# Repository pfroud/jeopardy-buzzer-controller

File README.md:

# Jeopardy buzzer controller

## About

For use with my [Jeopardy software](https://github.com/pfroud/jeopardy).

This device uses an Arduino to emulate a USB HID keyboard (like a QWERTY keyboard not a music keyboard). Instead of normal keyboard keys, the inputs come from rugged metal footswitches on long cables.

The sole purpose of this device is to convert physical button presses into USB HID keystrokes. It cannot tell which person buzzed first for a question, for example. All of that logic is done by software running on the host PC.

The PCB was designed using KiCad version 6 and fabricated by JLCPCB.

## Parts

The two most interesting parts are:

* [Sparkfun Pro Micro](https://www.sparkfun.com/products/12640) (not Mini, not Nano)
    * Informally called "Arduino Pro Micro" but it's actually a Sparkfun product which is Arduino-compatible.
    * To learn about the software running on the Arduino, see the [Arduino directory](Arduino).
* [XLR receptacle NC4MBV](https://www.neutrik.com/en/product/nc4mbv-1) to connect the buzzers.
    * To learn more, go to the "XLR connectors" section in this document.

Other parts:

* [12-pin female headers](https://www.aliexpress.us/item/2255801012106911.html) to hold the Arduino.
    * The Arduino could instead be soldered directly to the PCB if you're feeling confident.
* A toggle switch to enable/disable the Arduino software.
    * Lets you turn the buzzers off without unplugging the USB cable.
* [Panel-mount LED lights](https://www.aliexpress.com/item/3256803816108154.html) to indicate when it's powered and enabled.
* [2-pin pluggable terminal blocks](https://www.aliexpress.us/item/2251832631116561.html) to connect the toggle switch and indicator LEDs to the PCB.
* A 6mm tactile pushbutton to reset the Arduino.
    * The Pro Micro does not have a built-in reset button.

Then everything gets assembled into an [enclosure](docs/enclosure.md).

## Buzzers

On the Jeopardy TV show each contestant holds a thumb-operated buzzer ([source](https://www.jeopardy.com/jbuzz/behind-scenes/how-does-jeopardy-buzzer-work)).

My game has teams instead of individual players, so the buzzers rest on a table for access by all team members. I got rugged metal footswitches to withstand being slammed when someone thinks of an answer.

I started with Treadlite footswitches from at HSC Electronics (RIP) then got some TEMCo ones from [eBay](https://www.ebay.com/itm/372481343124).

On each footswitch I had to grind down the metal housing a little to fit a [PG7 cord grip](https://www.ebay.com/itm/222727122407). (PG stands for [Panzergewinde](https://en.wikipedia.org/wiki/Panzergewinde) which is an old German thread standard inexplicably still in use.)

The Treadlite model (below left) has a seemingly-custom switch mechanism inside, while the TEMCo model (below right) has a standard limit switch. The Treadlite ones originally come with *two* switches mounted at different heights but I removed the lower ones. The cable I used has a foil shield so I connected the drain wire to the metal housing for fun.

Eight buzzers are supported although I rarely use more than six.

## Known bugs & future work

### PCB design

* There is no input protection on the Arduino pins.
* The trace length between the Arduino and XLR connector is different for each connector.

### Does using an HID keyboard for this make any sense??

Not really. The original scope of my [Jeopardy project](https://github.com/pfroud/jeopardy) was software only. The hardware buzzers have been gradually developed as needed. Want to keep it simple!

See docs/dont-use-a-HID-keyboard.md.

### Issues with the XLR connectors

XLR connectors are usually used in professional audio and stage lighting, so they are overkill for this application. I wanted locking connectors and found these in surplus.

#### Wasted pins

Only two out of four pins are used. In the future, the spare pins could be used for lighting or some other new feature. An overwhelming number of two-pin locking connectors are available.

#### Polarity

The polarity of the XLR connectors should be reversed.

Neutrik makes four types of 4-pin XLR connectors. Look at the table below for a visual aid.

The receptacles on the controller are male (top left, NC4MBV) which allows fingers to touch the pins, exposing the Arduino to static electricity.

Meanwhile the connectors on the buzzer cables are female (bottom right, NC4FXX). The recessed pins prevent fingers touching them, but that protection isn't needed because the buzzers contain only passive switches.

The controller should use female receptacles, and the buzzers should use male cable connectors.

<table>
<tr>
    <td></td>
    <td align="center">Male</td>
    <td align="center">Female</td>
</tr>
<tr>
    <td>Receptacle</td>
    <td align="center">
        <a href="https://www.neutrik.us/en-us/product/nc4mbv-1">
            
            <br>
            NC4MBV
        </a>
    </td>
    <td align="center">
        <a href="https://www.neutrik.us/en-us/product/nc4fbv">
            
            <br>
            NC4FBV
        </a>
    </td>
</tr>
<tr>
    <td>Cable connector</td>
    <td align="center">
        <a href="https://www.neutrik.us/en-us/product/nc4mxx">
            
            <br>
            NC4MXX
        </a>
    </td>
    <td align="center">
        <a href="https://www.neutrik.us/en-us/product/nc4fxx">
            
            <br>
            NC4FXX
        </a>
    </td>
</tr>
</table>

## Previous versions of my Jeopardy buzzer controller

I made my first Jeopardy buzzer controller in 2018. It used the the PCB from an off-the-shelf USB keyboard (a QWERTY keyboard not a music keyboard) to convert physical button presses into USB HID keystrokes.

Inside the case of a broken power tool battery charger was a tangle of wires and Wago lever nuts. I used barrel jacks intended for DC power to connect the buzzers because they were easily available. This worked acceptably well but looked crazy:

In 2020 re-did the enclosure and wiring but kept using barrel jacks:

Inside the new enclosure, I upgraded to a prototype board and pluggable wire-to-board connectors. The USB keyboard PCB is visible on the left:

In 2022 I re-did the whole thing with a custom PCB and Arduino (which is this repository).

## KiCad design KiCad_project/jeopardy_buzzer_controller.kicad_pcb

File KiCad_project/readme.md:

# KiCad project

Pictures of the PCB:

<table>
<tr>
<td></td>
<td></td>
</tr>
<tr>
<td></td>
<td></td>
</tr>
</table>

Only eight buzzers are supported and the Arduino has twelve digital I/O pins, so no [matrix circuit](https://en.wikipedia.org/wiki/Keyboard_matrix_circuit) is needed.

## Schematic screenshots

Here are screenshots of the schematic so you don't need to download / install / launch KiCad:

<table>
<tr>
<td></td>
<td></td>
</tr>
</table>

## XLR connector

They are [Neutrik NC4MBV](https://www.neutrik.com/en/product/nc4mbv-1) which are:

> 4 pole male XLR receptacle, grounding: separate ground contact to mating connector shell and front panel.

Each connector has four cylindrical pins with shoulders. A rectangular tab on the bottom contacts the shell of the mating connector.

KiCad comes with symbols & footprints for 4-pin XLR connectors; I modified both slightly.

### Symbol

I added a ground pin to the "XLR4" symbol in the KiCad [Connector](https://kicad.github.io/symbols/Connector) library:

### Footprint

I started with the "Jack_XLR_Neutrik_NC4MBV_Vertical" footprint in the KiCad [Connector_Audio](https://kicad.github.io/footprints/Connector_Audio) library, which  exactly matches the footprint provided by Neutrik.

After the PCB was fabricated, I saw that those dimensions hold the connector about  &frac14; inch (6 mm) above the board. The shoulders of the cylindrical pins and the square section of the ground tab both rest on the PCB surface. I think this looks sort of silly and expected the black plastic housing to touch the board.

To see a comparison, I drilled out the pads on an extra board. In the pictures below, the original footprint is on the left and the footprint with drilled-out holes is on the right:

<table>
<tr>
<td></td>
<td></td>
</tr>
</table>

I edited the footprint to make the black plastic housing touch the PCB. First I increased the sizes of pads 1-4 so the full diameter of the cylinder could go through the board. Then I changed the ground pin from a circle to a slot to let the bigger non-square part of the ground tab go through as well.

But I never got a board fabricated with the modified footprint! When assembling the PCB into the [enclosure](../docs/enclosure.md), I discovered that having the connectors on long legs was actually very helpful because they could bend slightly to accommodate imperfect hole alignment in the plastic wall.

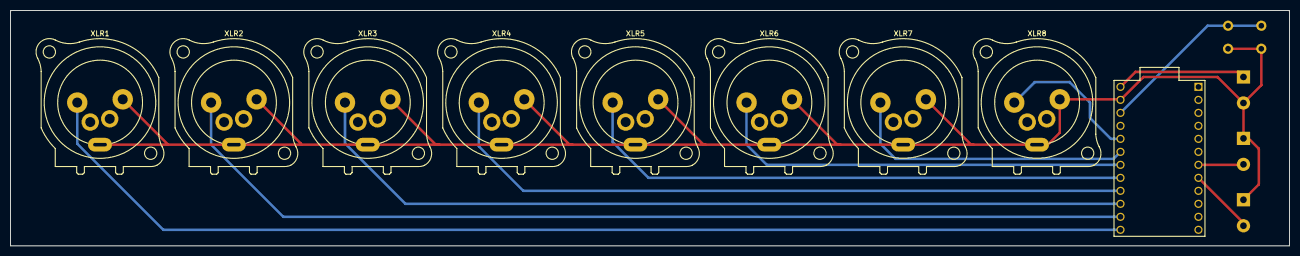
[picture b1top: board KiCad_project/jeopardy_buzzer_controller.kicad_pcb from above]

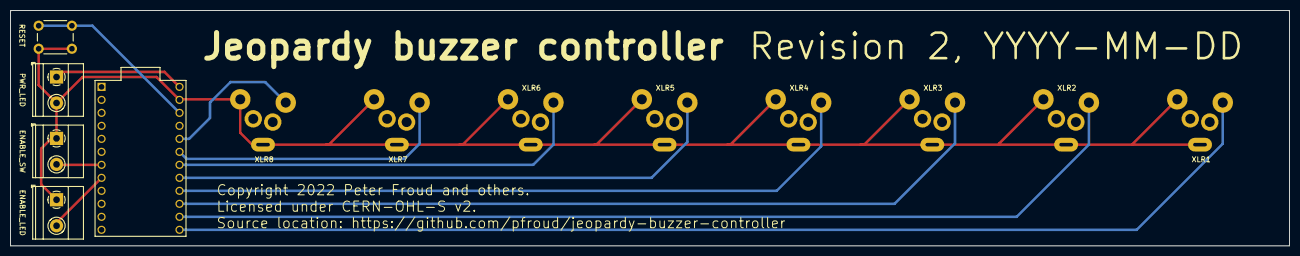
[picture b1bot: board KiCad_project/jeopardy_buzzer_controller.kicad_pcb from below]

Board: 2 copper layers, 250.0 x 46.0 mm, 13 parts (5 on the bottom side), 13 nets.

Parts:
J11: ENABLE_SW; TerminalBlock_Phoenix_MKDS-1,5-2-5.08_1x02_P5.08mm_Horizont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
J12: ENABLE_LED; TerminalBlock_Phoenix_MKDS-1,5-2-5.08_1x02_P5.08mm_Horizont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
J13: PWR_LED; TerminalBlock_Phoenix_MKDS-1,5-2-5.08_1x02_P5.08mm_Horizont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
SW1: RESET; SW_PUSH_6mm
U1: Arduino Pro Micro; ProMicro
XLR1: XLR1; Jack_XLR_Neutrik_NC4MBV_Vertical_with_bigger_holes
XLR2: XLR2; Jack_XLR_Neutrik_NC4MBV_Vertical_with_bigger_holes
XLR3: XLR3; Jack_XLR_Neutrik_NC4MBV_Vertical_with_bigger_holes
XLR4: XLR4; Jack_XLR_Neutrik_NC4MBV_Vertical_with_bigger_holes
XLR5: XLR5; Jack_XLR_Neutrik_NC4MBV_Vertical_with_bigger_holes
XLR6: XLR6; Jack_XLR_Neutrik_NC4MBV_Vertical_with_bigger_holes
XLR7: XLR7; Jack_XLR_Neutrik_NC4MBV_Vertical_with_bigger_holes
XLR8: XLR8; Jack_XLR_Neutrik_NC4MBV_Vertical_with_bigger_holes

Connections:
/XLR1: U1.13 (B6), XLR1.1
/XLR2: U1.14 (B2), XLR2.1
/XLR3: U1.15 (B3), XLR3.1
/XLR4: U1.16 (B1), XLR4.1
/XLR5: U1.17 (F7), XLR5.1
/XLR6: U1.18 (F6), XLR6.1
/XLR7: U1.19 (F5), XLR7.1
/XLR8: U1.20 (F4), XLR8.1
GND: J11.1, J12.1, J13.2, SW1.2, U1.23 (GND), XLR1.4, XLR1.G, XLR2.4, XLR2.G, XLR3.4, XLR3.G, XLR4.4, XLR4.G, XLR5.4, XLR5.G, XLR6.4, XLR6.G, XLR7.4, XLR7.G, XLR8.4, XLR8.G
unnamed: J11.2, U1.7 (D4)
unnamed: J12.2, U1.8 (C6)
unnamed: J13.1, U1.24 (RAW)
unnamed: SW1.1, U1.22 (RST)

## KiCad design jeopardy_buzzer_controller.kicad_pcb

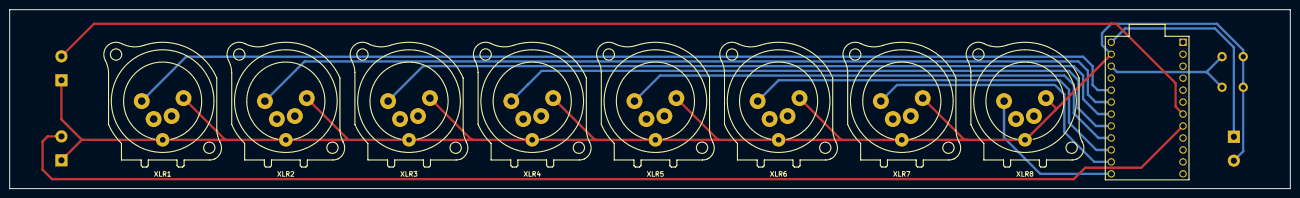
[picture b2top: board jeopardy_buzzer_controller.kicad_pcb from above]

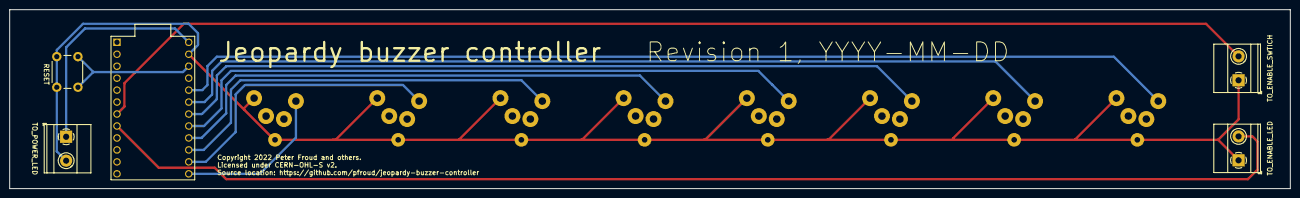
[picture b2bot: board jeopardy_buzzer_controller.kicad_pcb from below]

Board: 2 copper layers, 272.0 x 38.0 mm, 13 parts (5 on the bottom side), 13 nets.

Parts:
J1: XLR1; Jack_XLR_Neutrik_NC4MBV_Vertical
J2: XLR2; Jack_XLR_Neutrik_NC4MBV_Vertical
J3: XLR3; Jack_XLR_Neutrik_NC4MBV_Vertical
J4: XLR4; Jack_XLR_Neutrik_NC4MBV_Vertical
J5: XLR5; Jack_XLR_Neutrik_NC4MBV_Vertical
J6: XLR6; Jack_XLR_Neutrik_NC4MBV_Vertical
J7: XLR7; Jack_XLR_Neutrik_NC4MBV_Vertical
J8: XLR8; Jack_XLR_Neutrik_NC4MBV_Vertical
J11: TO_ENABLE_SWTICH; TerminalBlock_Phoenix_MKDS-1,5-2-5.08_1x02_P5.08mm_Horizont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
J12: TO_ENABLE_LED; TerminalBlock_Phoenix_MKDS-1,5-2-5.08_1x02_P5.08mm_Horizont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
J13: TO_POWER_LED; TerminalBlock_Phoenix_MKDS-1,5-2-5.08_1x02_P5.08mm_Horizont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
SW1: RESET; SW_PUSH_6mm
U1: Arduino Pro Micro; ProMicro

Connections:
/XLR1: J1.1, U1.20 (F4)
/XLR2: J2.1, U1.19 (F5)
/XLR3: J3.1, U1.18 (F6)
/XLR4: J4.1, U1.17 (F7)
/XLR5: J5.1, U1.16 (B1)
/XLR6: J6.1, U1.15 (B3)
/XLR7: J7.1, U1.14 (B2)
/XLR8: J8.1, U1.13 (B6)
GND: J1.4, J1.G, J2.4, J2.G, J3.4, J3.G, J4.4, J4.G, J5.4, J5.G, J6.4, J6.G, J7.4, J7.G, J8.4, J8.G, J11.1, J12.1, J13.2, SW1.2, U1.23 (GND)
unnamed: J11.2, U1.7 (D4)
unnamed: J12.2, U1.8 (C6)
unnamed: J13.1, U1.24 (RAW)
unnamed: SW1.1, U1.22 (RST)

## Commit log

2022-07-20 Add power LED, enable switch, enable LED
2022-07-20 Add 3D model of pluggable screw terminal block
2022-07-20 Move Arduino Pro Micro library to Git submodule
2022-07-20 Move 3D models to subfolder
2022-07-20 Update links to 3D models
2022-07-31 Add arduino sketch
2022-07-31 Fix closing comment
2022-07-31 Got Arduino sketch working
2022-08-08 Add enable light to arduino sketch
2022-08-15 Figured out sensible layout for everything
2022-08-15 Route tracks
2022-08-15 Clean up silkscreen
2022-08-15 Add CERN OHL2-S license
2022-08-15 Add title text w/ revision number and date
2022-08-15 Move 3D model sources from txt file to markdown
2022-08-15 Move KiCad project into own directory
2022-08-15 Put Arduino Kicad library back in as git submodule
2022-08-19 Vertically center XLR connectors in downspout
2022-08-23 Add date stamp and generate gerbers!
2022-09-06 Increase font size and thickness
2022-09-06 Add custom XLR footprint with bigger holes
    Adding a modified version of the "Jack_XLR_Neutrik_NC4MBV_Vertical"
    footprint included in the KiCad "Connector_Audio" library.
    The NC4MBV footprint included with KiCad uses hole sizes specified by
    Neutrik here: https://www.neutrik.com/en/product/nc4mbv-1
    Pins 1 through 4 are cylindrical, with a double-taper on the tip
    and then a shoulder. The ground pin is rectangular with a shoulder only.
2022-09-06 Fix silkscreen intersecting pad
2022-09-07 Fix pin mapping between KiCad and Arduino
2022-09-28 Add debug printing to serial
2022-09-28 First attempt adding debouncing
2022-09-29 Add lots of debugging printouts
2022-09-29 Remove printouts, shorten debounce delay to 5 ms
2022-09-29 Release keyboard keys when disabled
2023-04-08 Add screenshots of kicad schematic
2023-12-26 Remove dimensions of unused enclosure from PCB
2024-07-07 Add documentation and pictures
2024-07-07 Fix case-sensitive path
2024-07-07 Fix more case-sensitive file paths
2024-07-17 Add documentation
2024-07-17 Add image border
2024-07-17 Use markdownlint
2024-07-19 Increase image size from 1000px to 2000px width
2024-07-19 Rename images
2024-07-25 Move poll rate images; clarify poll vs scan rate
2024-07-30 Add documentation about buzzers
2024-07-31 Rename directory of screws for XLR connectors
2024-11-03 Add heading for schematic screenshots
2024-11-22 Add docs about XLR connector footprint
2024-11-22 Adjust image sizes and alt text
2024-11-22 Add docs about previous versions of the controller
2024-11-22 Add links between doc files

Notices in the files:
KiCad_project/jeopardy_buzzer_controller.kicad_pcb:
Copyright 2022 Peter Froud and others.
Licensed under CERN-OHL-S v2.
Copyright Peter Froud 2022.
This source describes Open Hardware and is licensed under the CERN-OHL-S v2.
You may redistribute and modify this source and make products using it under
the terms of the CERN-OHL-S v2 (https://ohwr.org/cern_ohl_s_v2.txt).
